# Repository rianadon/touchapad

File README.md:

# Touchapad

Touchapad is an touchscreen-based button pad designed to be placed outdoors and control [Home Assistant](https://home-assistant.io) devices.

This repository hosts the code used for:
 - The Arduino controlling the touchscreen
 - STL files for 3D-printed parts
 - KiCad files for the Arduino shield. You can download KiCad to export Gerber files configured to however your PCB manufacturer requires.
 - Python server for linking the Arduino touchscreen to Home Assistant and serving the configuration frontend
 - Configuration frontend source code (uses Svelte so you've got to compile it)

Design and architecture information can be found at the project's [blog post](https://rianadon.github.io/blog/2020/05/23/touchapad.html).

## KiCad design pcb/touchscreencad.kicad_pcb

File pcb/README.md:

# PCB files

These files were generated using KiCad. You can use the same software to generate the gerbers and drill files, which I've omitted.

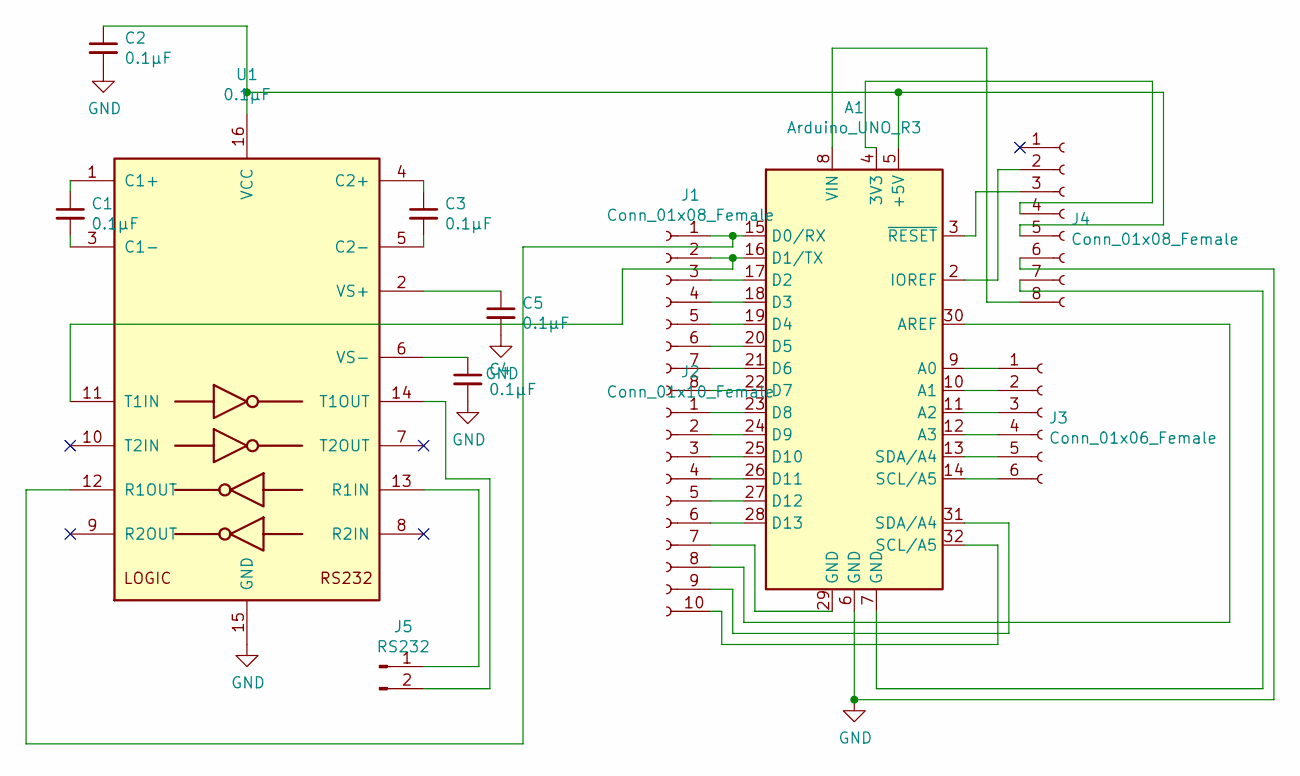
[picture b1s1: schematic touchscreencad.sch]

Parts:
A1: Arduino_UNO_R3
C1, C2, C3, C4, C5: 0.1μF; C_0402_1005Metric
J1: Conn_01x08_Female; PinHeader_1x08_P2.54mm_Vertical
J2: Conn_01x10_Female; PinHeader_1x10_P2.54mm_Vertical
J3: Conn_01x06_Female; PinHeader_1x06_P2.54mm_Vertical
J4: Conn_01x08_Female; PinSocket_1x08_P2.54mm_Vertical
J5: RS232; PinSocket_1x02_P2.54mm_Horizontal
U1: 0.1μF; SOIC-16_3.9x9.9mm_P1.27mm

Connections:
GND: A1.6 (GND), C2.2, C4.2, C5.2, J4.6, U1.15 (GND)
unnamed: A1.2 (IOREF), J4.2
unnamed: A1.3 (~RESET), J4.3
unnamed: A1.4 (3V3), J4.4
unnamed: A1.5 (+5V), C2.1, J4.5, U1.16 (VCC)
unnamed: A1.7 (GND), J4.7
unnamed: A1.8 (VIN), J4.8
unnamed: A1.9 (A0), J3.1
unnamed: A1.10 (A1), J3.2
unnamed: A1.11 (A2), J3.3
unnamed: A1.12 (A3), J3.4
unnamed: A1.13 (SDA/A4), J3.5
unnamed: A1.14 (SCL/A5), J3.6
unnamed: A1.15 (D0/RX), J1.1, U1.12 (R1OUT)
unnamed: A1.16 (D1/TX), J1.2, U1.11 (T1IN)
unnamed: A1.17 (D2), J1.3
unnamed: A1.18 (D3), J1.4
unnamed: A1.19 (D4), J1.5
unnamed: A1.20 (D5), J1.6
unnamed: A1.21 (D6), J1.7
unnamed: A1.22 (D7), J1.8
unnamed: A1.23 (D8), J2.1
unnamed: A1.24 (D9), J2.2
unnamed: A1.25 (D10), J2.3
unnamed: A1.26 (D11), J2.4
unnamed: A1.27 (D12), J2.5
unnamed: A1.28 (D13), J2.6
unnamed: A1.29 (GND), J2.7
unnamed: A1.30 (AREF), J2.8
unnamed: A1.31 (SDA/A4), J2.9
unnamed: A1.32 (SCL/A5), J2.10
unnamed: C1.1, U1.1 (C1+)
unnamed: C1.2, U1.3 (C1-)
unnamed: C3.1, U1.4 (C2+)
unnamed: C3.2, U1.5 (C2-)
unnamed: C4.1, U1.6 (VS-)
unnamed: C5.1, U1.2 (VS+)
unnamed: J5.1, U1.13 (R1IN)
unnamed: J5.2, U1.14 (T1OUT)

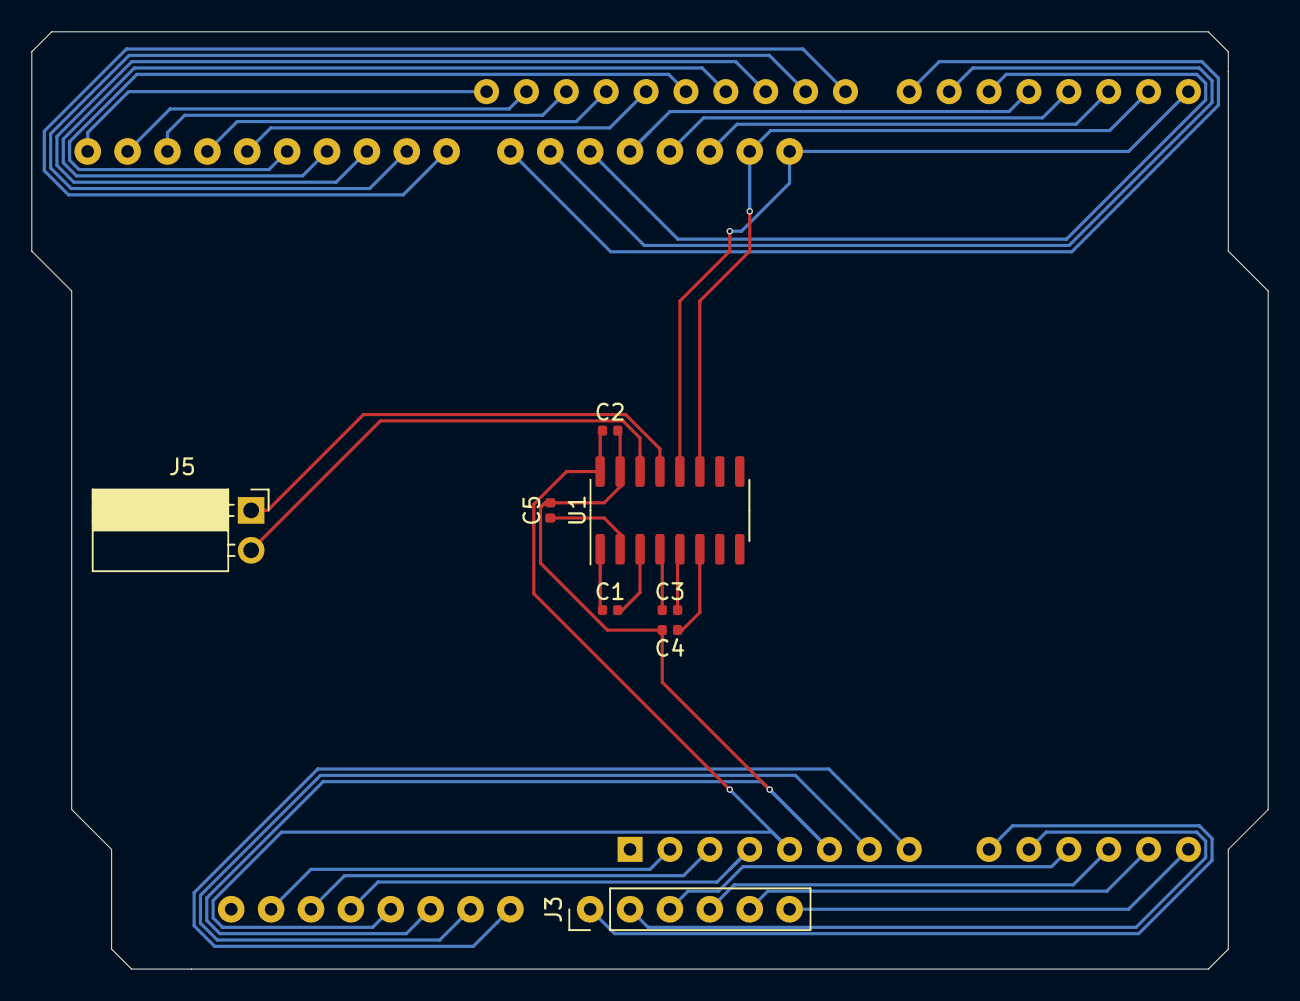
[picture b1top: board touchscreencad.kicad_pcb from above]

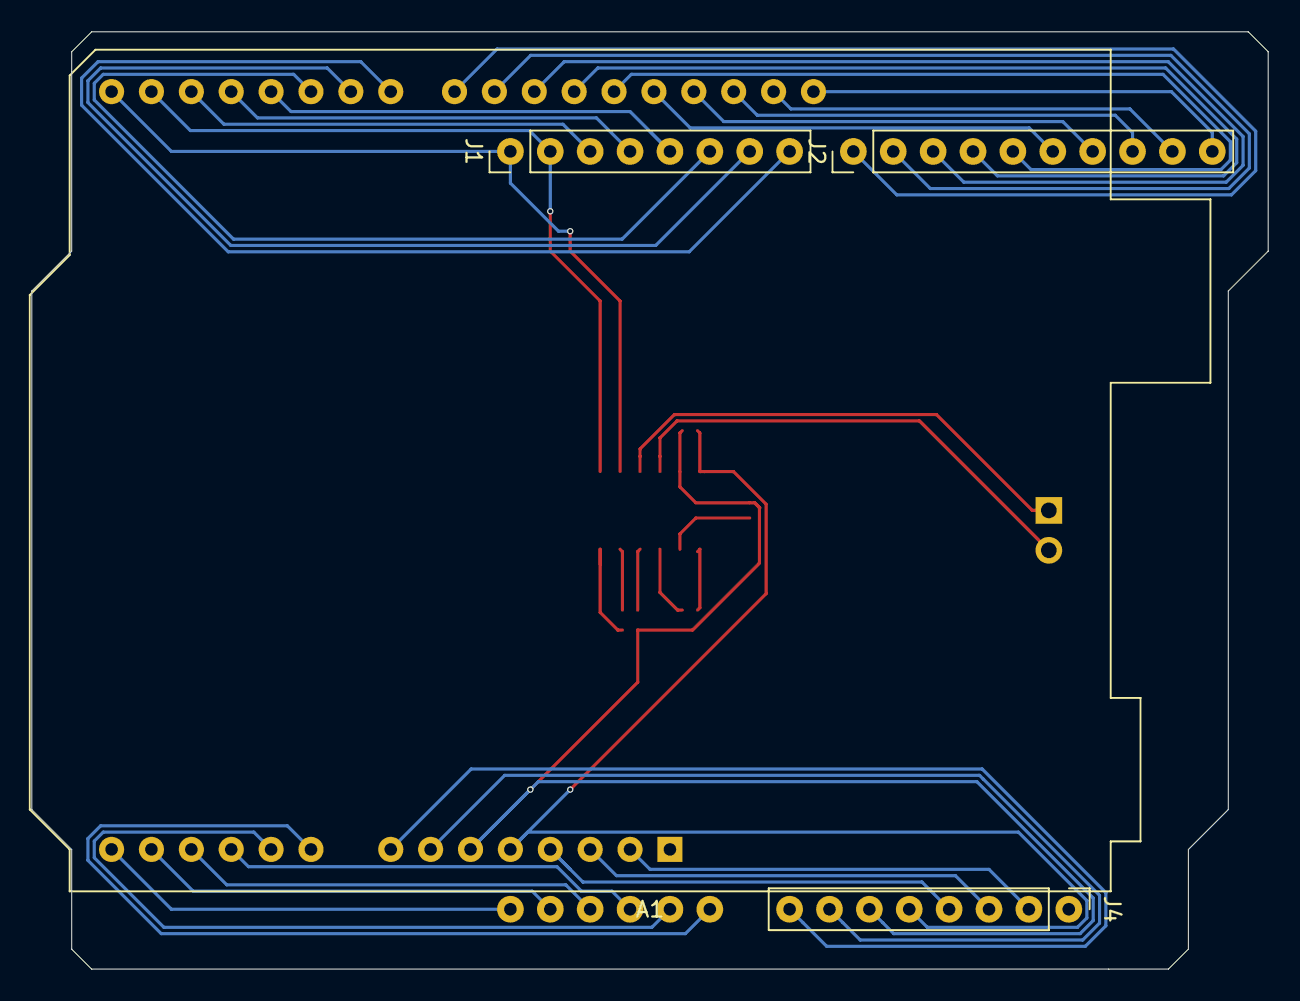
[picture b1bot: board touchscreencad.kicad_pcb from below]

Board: 2 copper layers, 78.7 x 59.7 mm, 12 parts (4 on the bottom side), 39 nets.

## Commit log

2020-03-29 Only 99 bugfixes to go
2020-03-29 I forgot to add a README
2020-03-29 Add link to deployed site
2020-03-29 Add keypress listeners for touch buttons
2020-03-30 Hex is uppercase, tabindex is null
2020-05-22 Use uppercase hex numbers in messages
2020-05-22 Only redraw display when a button's state changes
2020-05-23 Add more documentation
2021-06-06 Bump ws from 6.2.1 to 6.2.2 in /web
    Bumps [ws](https://github.com/websockets/ws) from 6.2.1 to 6.2.2.
    - [Release notes](https://github.com/websockets/ws/releases)
    - [Commits](https://github.com/websockets/ws/commits)
    ---
    updated-dependencies:
    - dependency-name: ws
2021-08-12 Bump path-parse from 1.0.6 to 1.0.7 in /web
    Bumps [path-parse](https://github.com/jbgutierrez/path-parse) from 1.0.6 to 1.0.7.
    - [Release notes](https://github.com/jbgutierrez/path-parse/releases)
    - [Commits](https://github.com/jbgutierrez/path-parse/commits/v1.0.7)
    ---
    updated-dependencies:
    - dependency-name: path-parse
2022-02-17 Bump sanic from 19.12.2 to 20.12.6 in /server
    Bumps [sanic](https://github.com/sanic-org/sanic) from 19.12.2 to 20.12.6.
    - [Release notes](https://github.com/sanic-org/sanic/releases)
    - [Changelog](https://github.com/sanic-org/sanic/blob/main/CHANGELOG.rst)
    - [Commits](https://github.com/sanic-org/sanic/compare/v19.12.2...v20.12.6)
    ---
    updated-dependencies:
2022-05-26 Bump ujson from 2.0.3 to 5.2.0 in /server
    Bumps [ujson](https://github.com/ultrajson/ultrajson) from 2.0.3 to 5.2.0.
    - [Release notes](https://github.com/ultrajson/ultrajson/releases)
    - [Commits](https://github.com/ultrajson/ultrajson/compare/2.0.3...5.2.0)
    ---
    updated-dependencies:
    - dependency-name: ujson
2022-07-05 Bump ujson from 2.0.3 to 5.4.0 in /server
    Bumps [ujson](https://github.com/ultrajson/ultrajson) from 2.0.3 to 5.4.0.
    - [Release notes](https://github.com/ultrajson/ultrajson/releases)
    - [Commits](https://github.com/ultrajson/ultrajson/compare/2.0.3...5.4.0)
    ---
    updated-dependencies:
    - dependency-name: ujson
2022-07-15 Bump svelte from 3.20.1 to 3.49.0 in /web
    Bumps [svelte](https://github.com/sveltejs/svelte) from 3.20.1 to 3.49.0.
    - [Release notes](https://github.com/sveltejs/svelte/releases)
    - [Changelog](https://github.com/sveltejs/svelte/blob/master/CHANGELOG.md)
    - [Commits](https://github.com/sveltejs/svelte/compare/v3.20.1...v3.49.0)
    ---
    updated-dependencies:
2022-07-20 Bump terser from 4.6.7 to 4.8.1 in /web
    Bumps [terser](https://github.com/terser/terser) from 4.6.7 to 4.8.1.
    - [Release notes](https://github.com/terser/terser/releases)
    - [Changelog](https://github.com/terser/terser/blob/master/CHANGELOG.md)
    - [Commits](https://github.com/terser/terser/commits)
    ---
    updated-dependencies:
